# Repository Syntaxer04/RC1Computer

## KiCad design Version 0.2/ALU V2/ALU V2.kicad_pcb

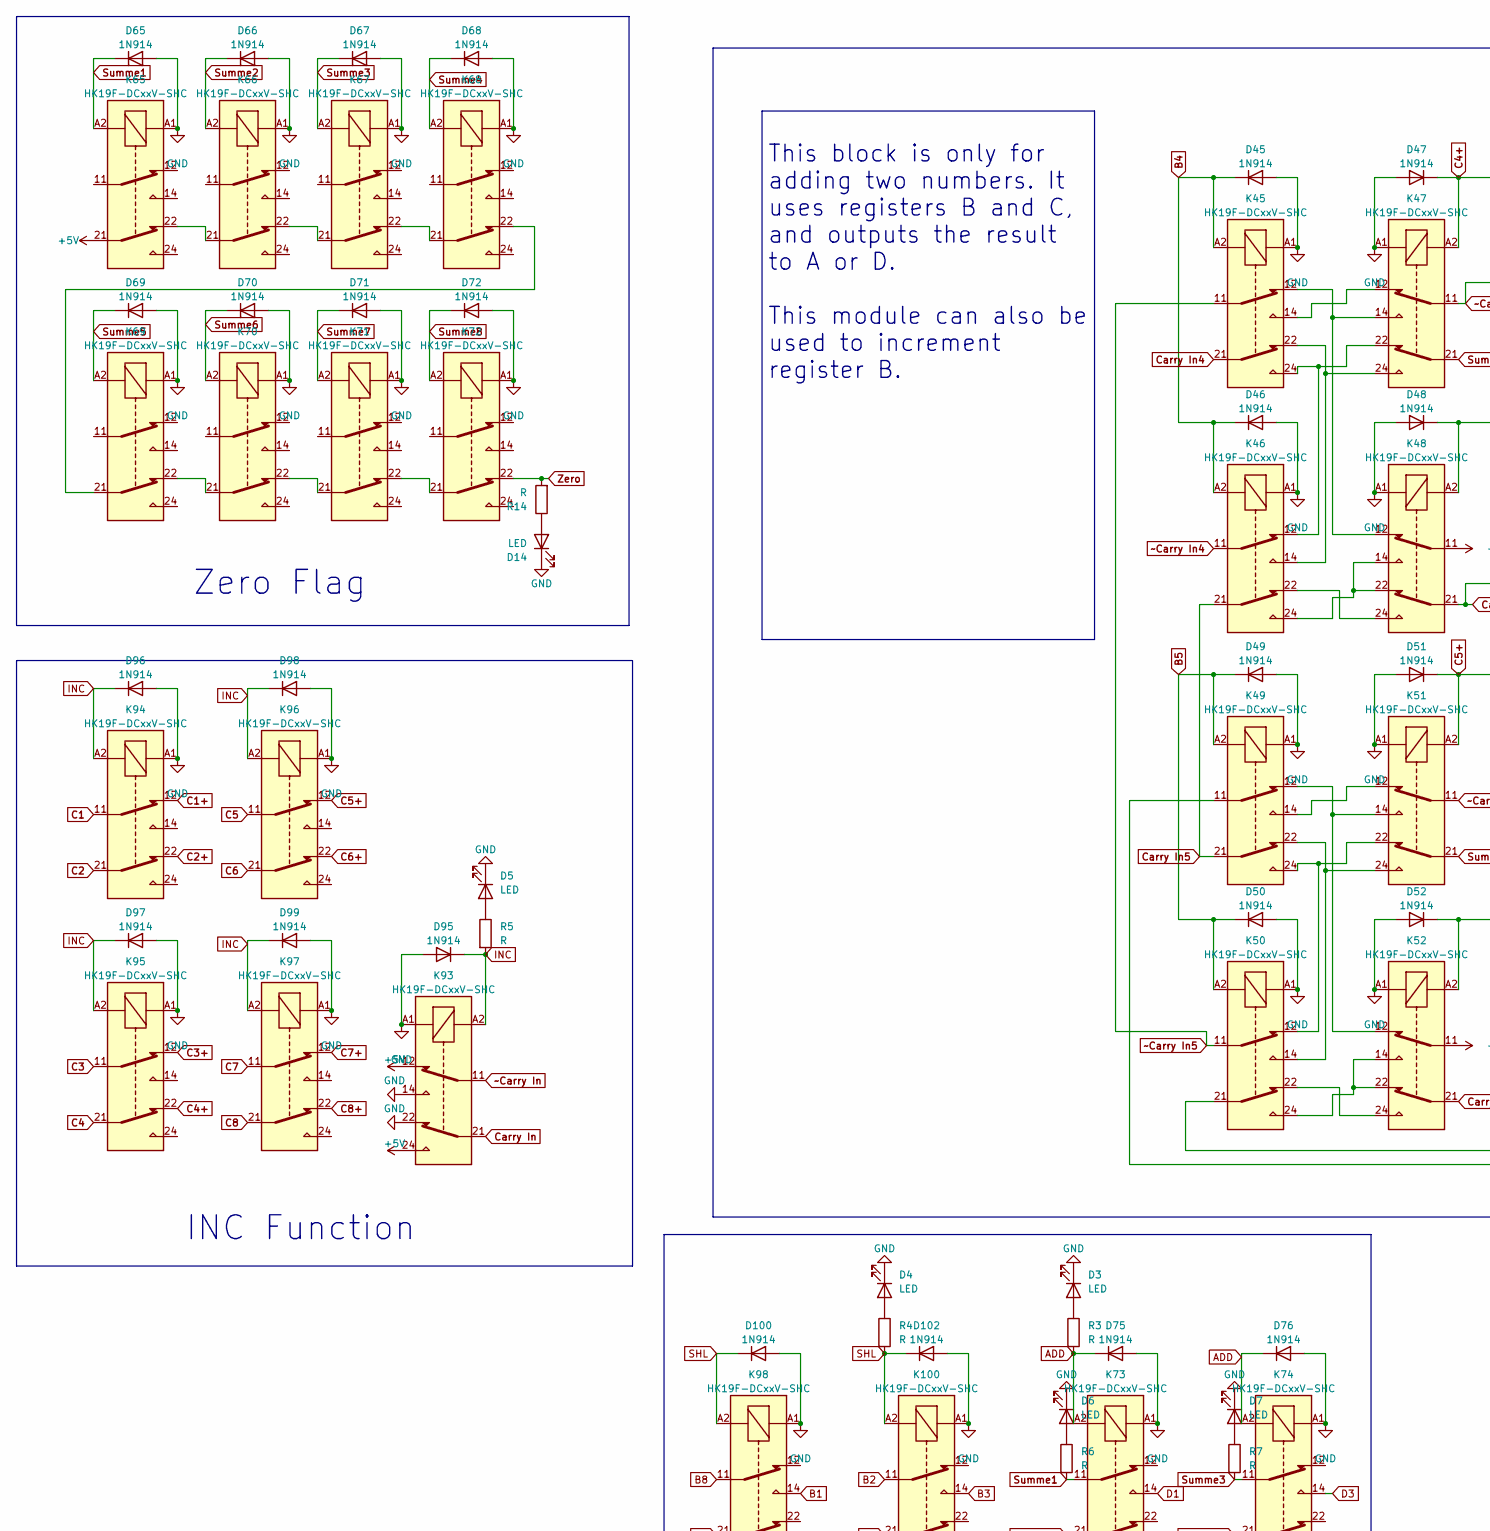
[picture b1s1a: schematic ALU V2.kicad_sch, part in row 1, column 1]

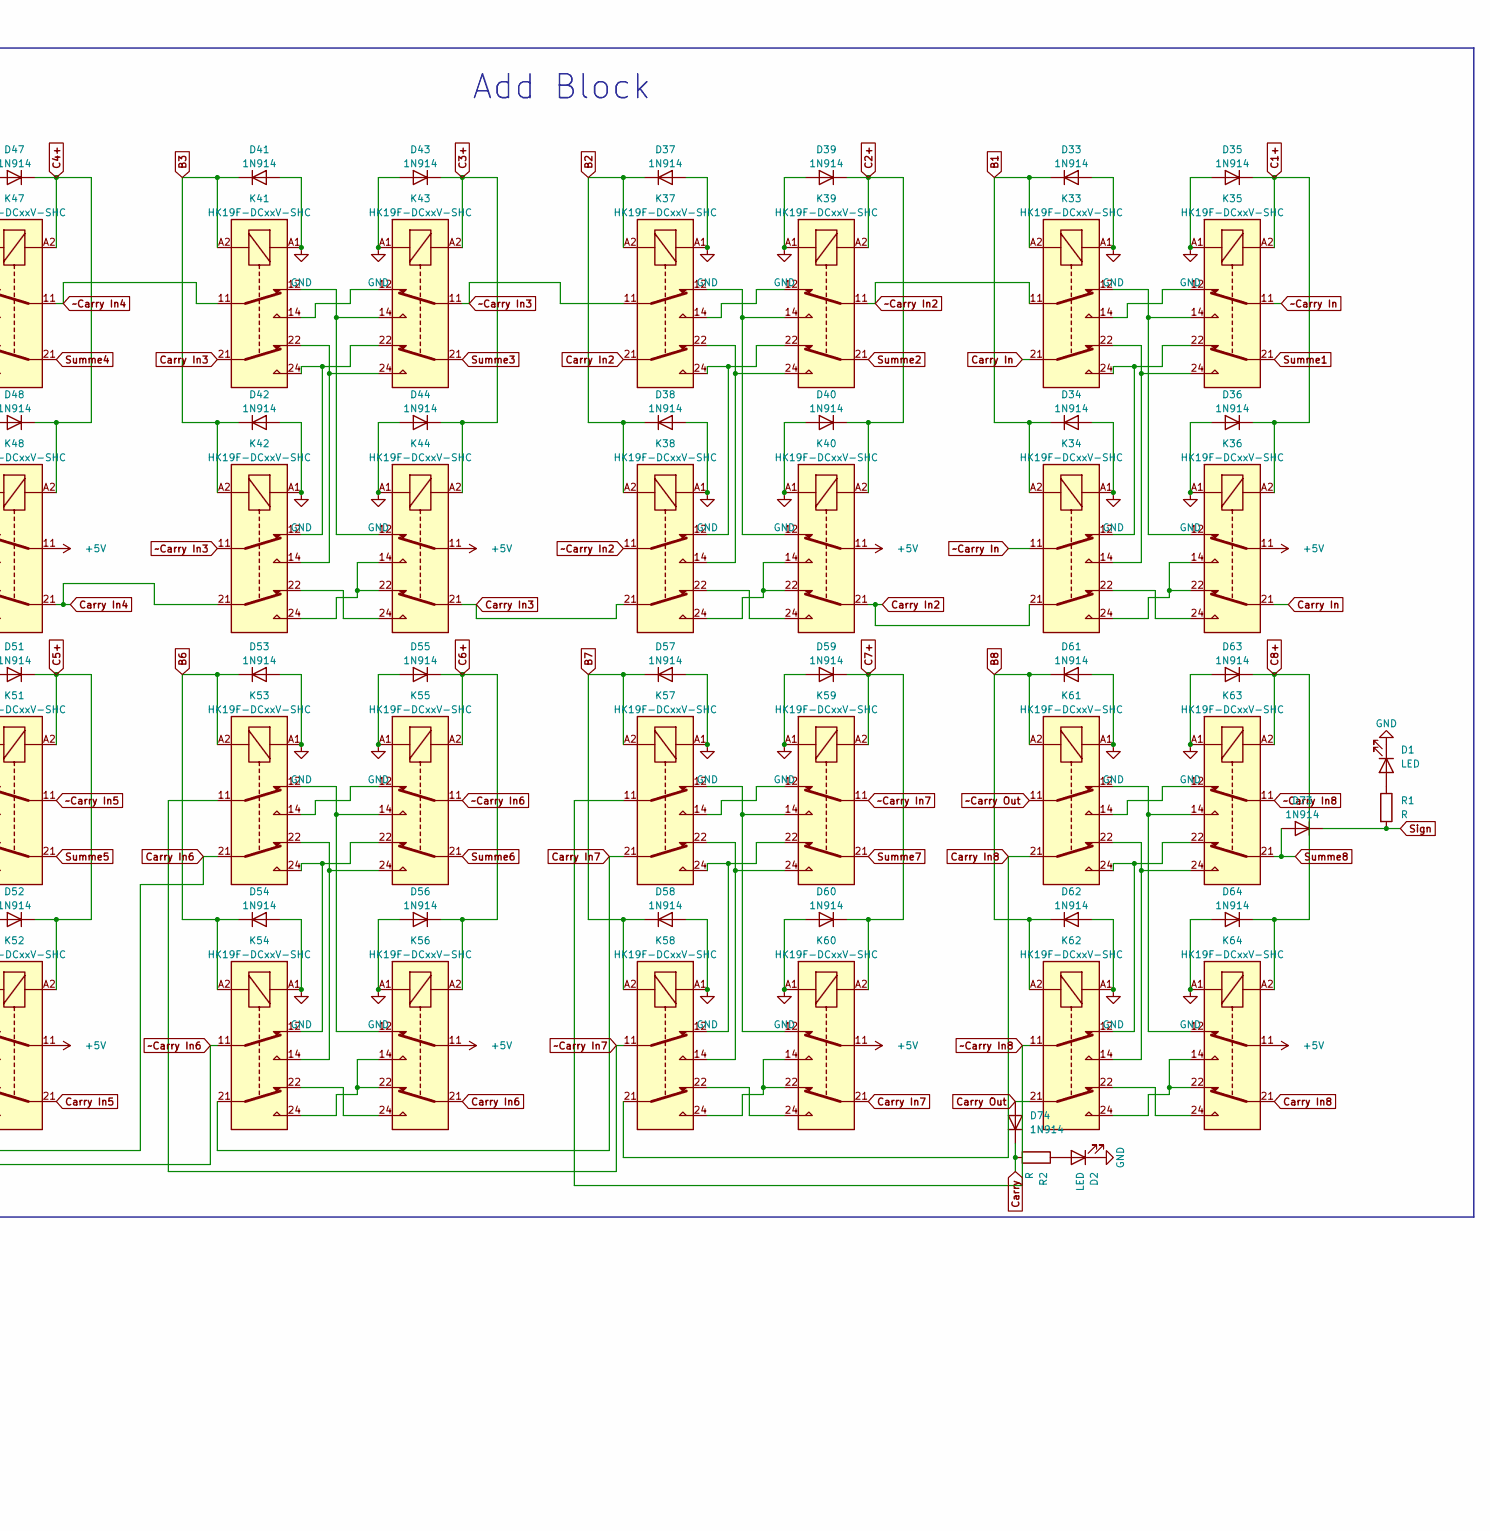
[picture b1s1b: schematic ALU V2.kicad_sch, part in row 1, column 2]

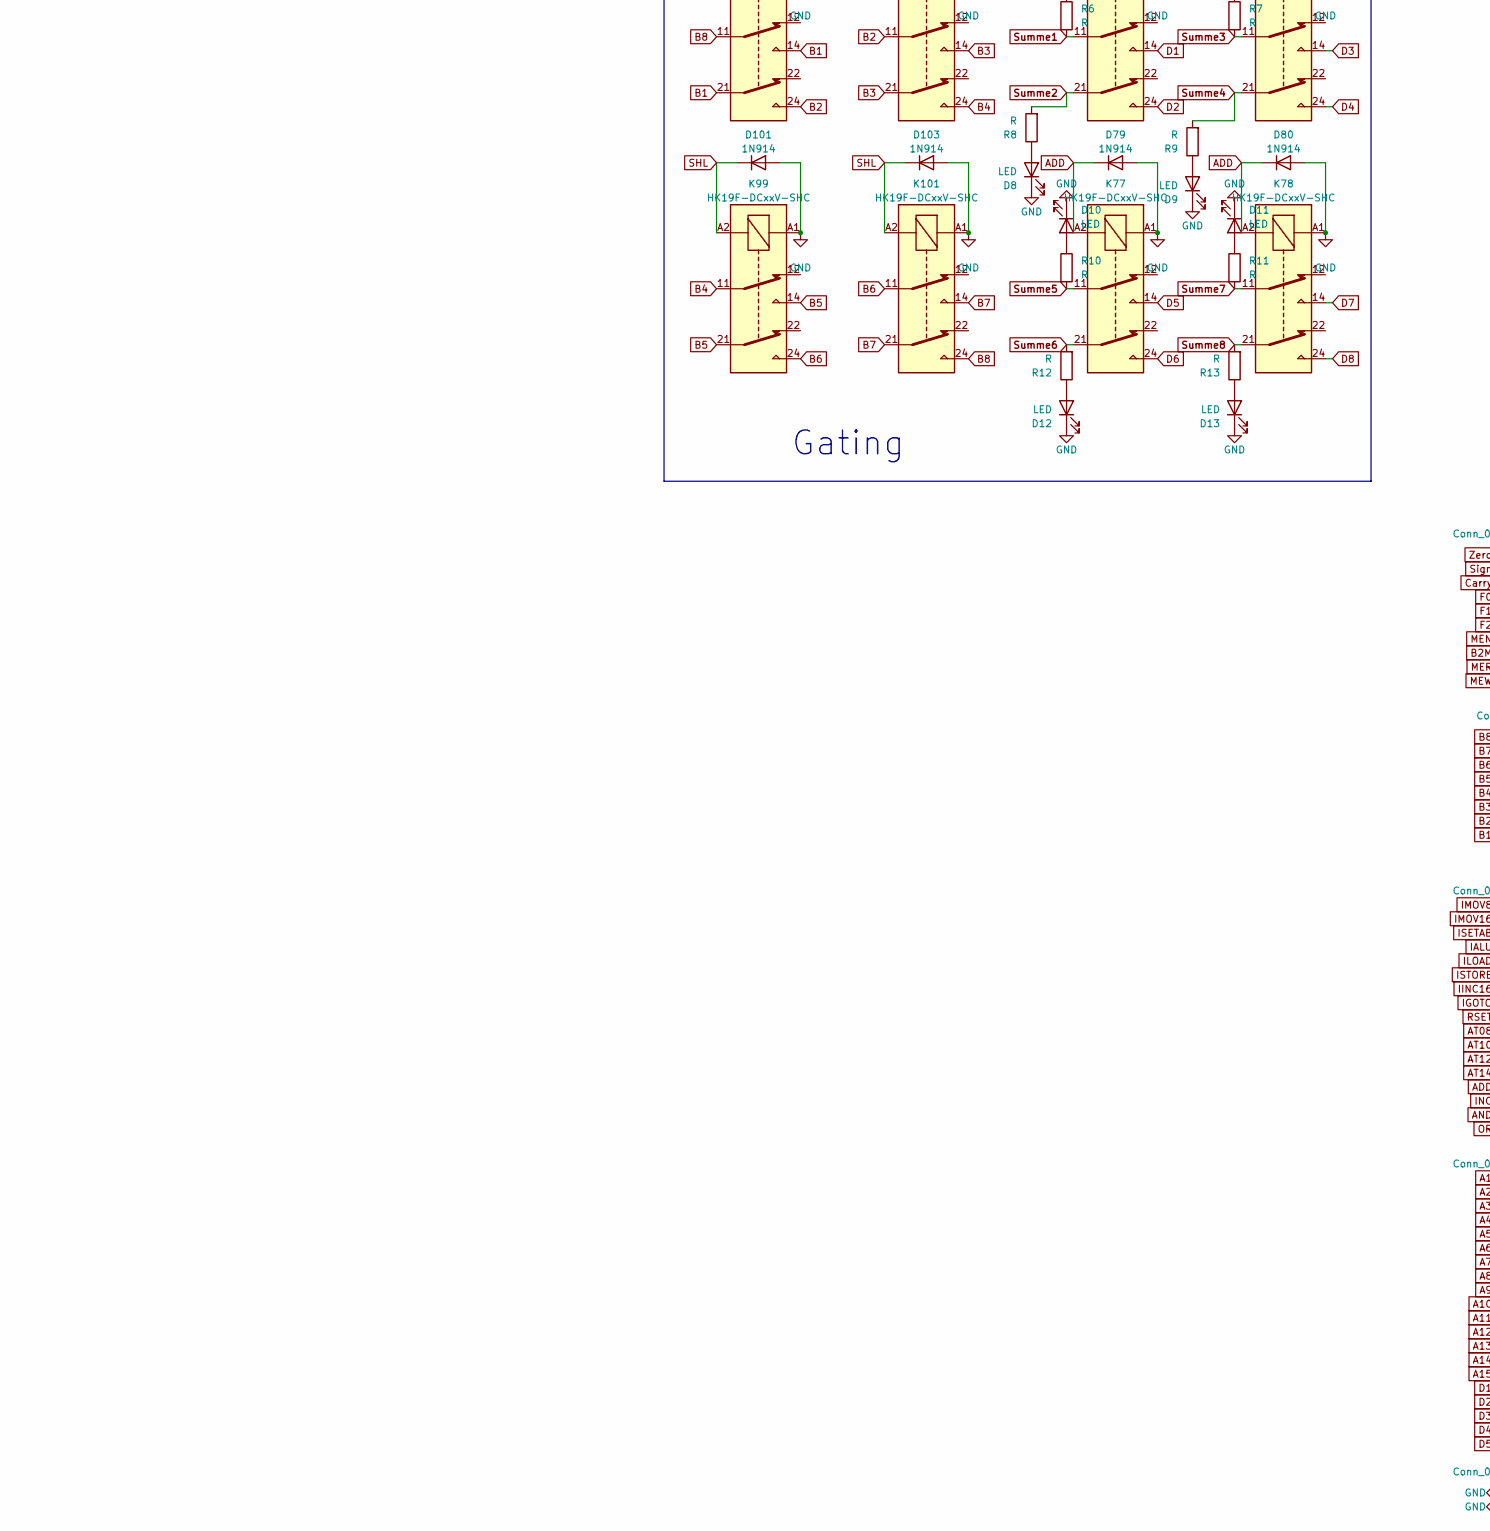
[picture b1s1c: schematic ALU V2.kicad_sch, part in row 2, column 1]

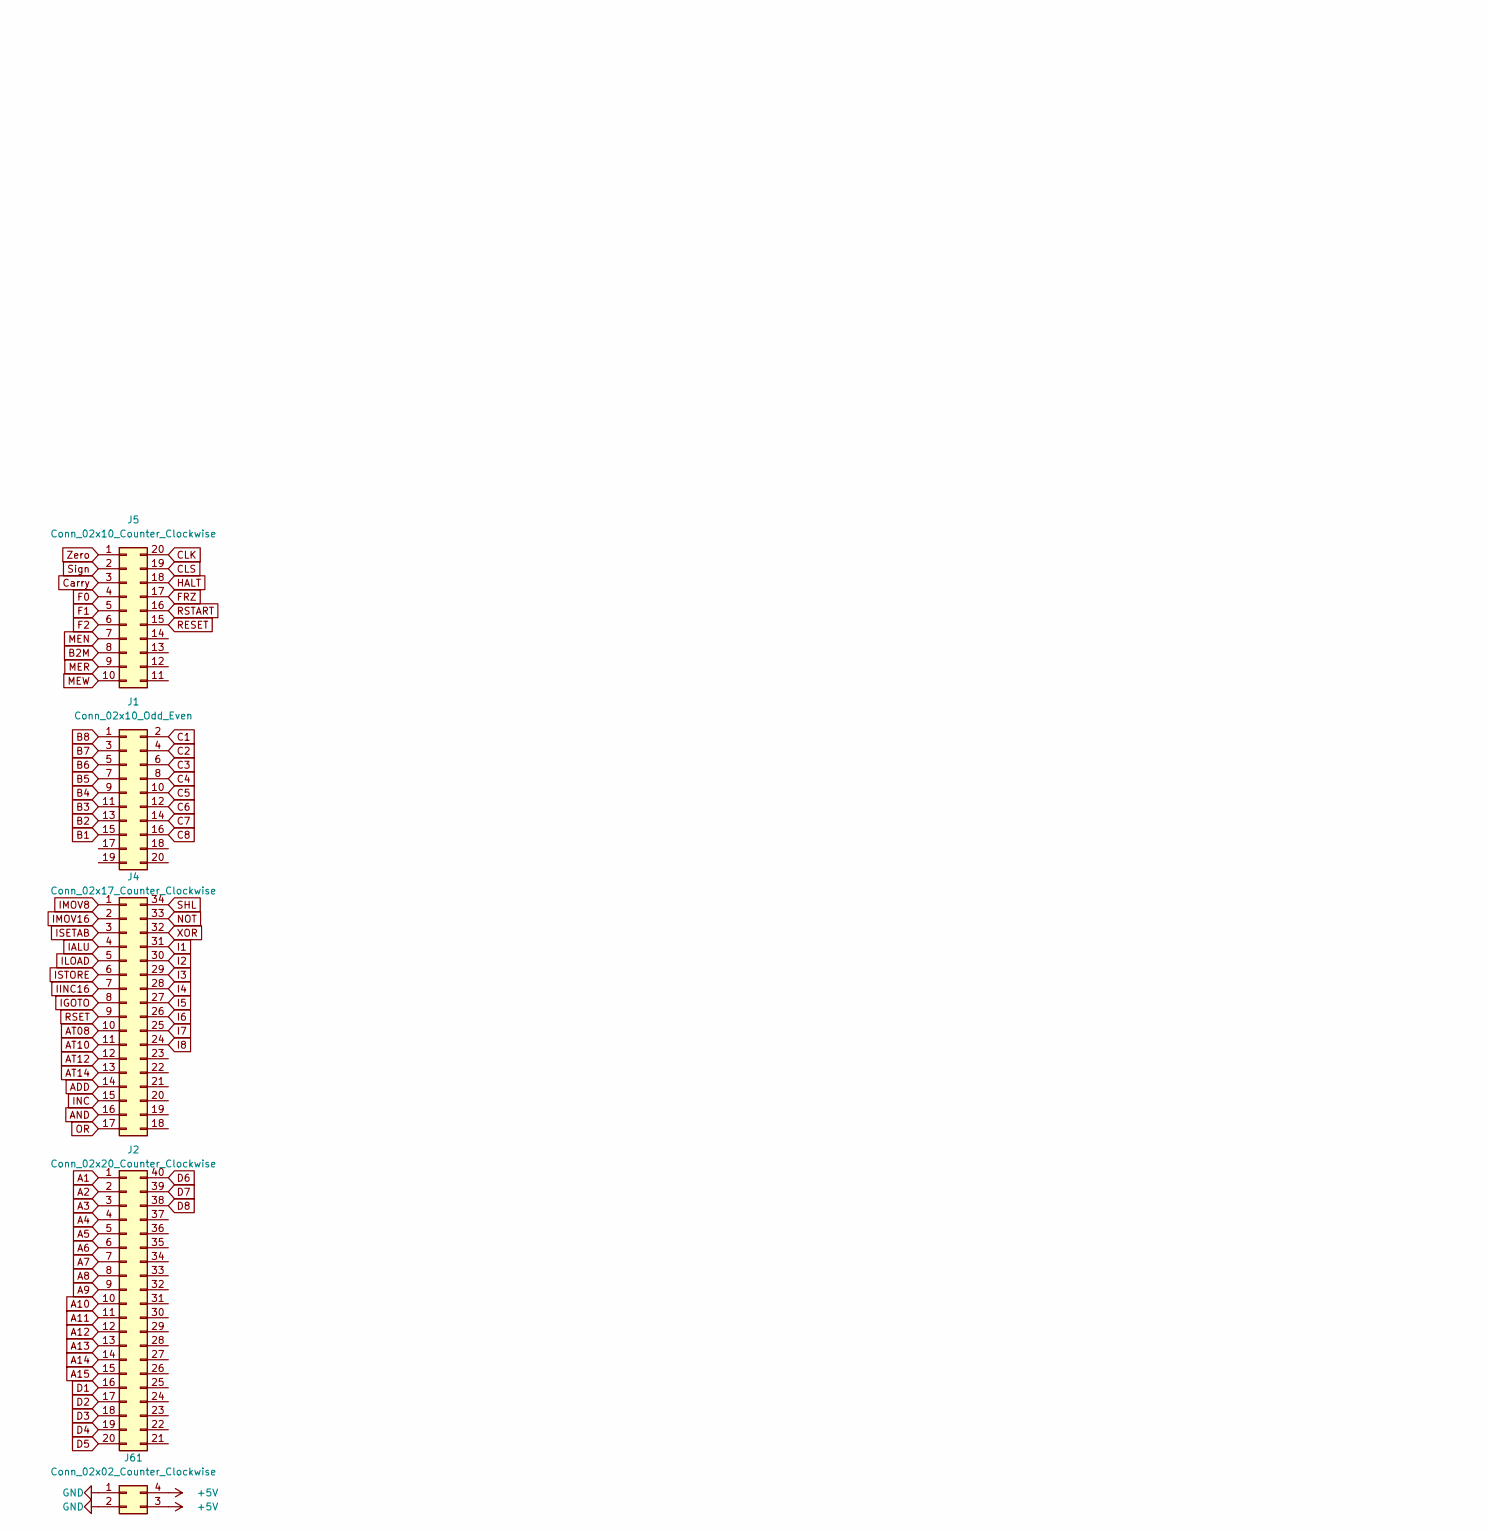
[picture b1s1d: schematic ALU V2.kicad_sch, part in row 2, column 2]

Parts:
D1, D2, D3, D4, D5, D6, D7, D8, D9, D10, D11, D12, D13, D14: LED; LED_D5.0mm
D33, D34, D35, D36, D37, D38, D39, D40, D41, D42, D43, D44, D45, D46, D47, D48, D49, D50, D51, D52, D53, D54, D55, D56, D57, D58, D59, D60, D61, D62, D63, D64, D65, D66, D67, D68, D69, D70, D71, D72, D73, D74, D75, D76, D79, D80, D95, D96, D97, D98, D99, D100, D101, D102, D103: 1N914; D_DO-35_SOD27_P7.62mm_Horizontal
J1: Conn_02x10_Odd_Even; PinHeader_2x10_P2.54mm_Horizontal
J2: Conn_02x20_Counter_Clockwise; PinSocket_2x20_P2.54mm_Horizontal
J4: Conn_02x17_Counter_Clockwise; PinSocket_2x17_P2.54mm_Horizontal
J5: Conn_02x10_Counter_Clockwise; PinSocket_2x10_P2.54mm_Horizontal
J61: Conn_02x02_Counter_Clockwise; PinSocket_2x02_P2.54mm_Horizontal
K33, K34, K35, K36, K37, K38, K39, K40, K41, K42, K43, K44, K45, K46, K47, K48, K49, K50, K51, K52, K53, K54, K55, K56, K57, K58, K59, K60, K61, K62, K63, K64, K65, K66, K67, K68, K69, K70, K71, K72, K73, K74, K77, K78, K93, K94, K95, K96, K97, K98, K99, K100, K101: HK19F-DCxxV-SHC; Relay_DPDT_Finder_30.22
R1, R2, R3, R4, R5, R6, R7, R8, R9, R10, R11, R12, R13, R14: R; R_Axial_DIN0204_L3.6mm_D1.6mm_P5.08mm_Horizontal

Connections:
+5V: J61.3, J61.4, K36.11, K40.11, K44.11, K48.11, K52.11, K56.11, K60.11, K64.11, K65.21, K93.12, K93.24
A1: J2.1
A2: J2.2
A3: J2.3
A4: J2.4
A5: J2.5
A6: J2.6
A7: J2.7
A8: J2.8
A9: J2.9
A10: J2.10
A11: J2.11
A12: J2.12
A13: J2.13
A14: J2.14
A15: J2.15
ADD: D75.1 (K), D76.1 (K), D79.1 (K), D80.1 (K), J4.14, K73.A2, K74.A2, K77.A2, K78.A2, R3.2
AND: J4.16
AT08: J4.10
AT10: J4.11
AT12: J4.12
AT14: J4.13
B1: D33.1 (K), D34.1 (K), J1.15, K33.A2, K34.A2, K98.14, K98.21
B2: D37.1 (K), D38.1 (K), J1.13, K37.A2, K38.A2, K98.24, K100.11
B2M: J5.8
B3: D41.1 (K), D42.1 (K), J1.11, K41.A2, K42.A2, K100.14, K100.21
B4: D45.1 (K), D46.1 (K), J1.9, K45.A2, K46.A2, K99.11, K100.24
B5: D49.1 (K), D50.1 (K), J1.7, K49.A2, K50.A2, K99.14, K99.21
B6: D53.1 (K), D54.1 (K), J1.5, K53.A2, K54.A2, K99.24, K101.11
B7: D57.1 (K), D58.1 (K), J1.3, K57.A2, K58.A2, K101.14, K101.21
B8: D61.1 (K), D62.1 (K), J1.1, K61.A2, K62.A2, K98.11, K101.24
C1: J1.2, K94.11
C1+: D35.1 (K), D36.1 (K), K35.A2, K36.A2, K94.12
C2: J1.4, K94.21
C2+: D39.1 (K), D40.1 (K), K39.A2, K40.A2, K94.22
C3: J1.6, K95.11
C3+: D43.1 (K), D44.1 (K), K43.A2, K44.A2, K95.12
C4: J1.8, K95.21
C4+: D47.1 (K), D48.1 (K), K47.A2, K48.A2, K95.22
C5: J1.10, K96.11
C5+: D51.1 (K), D52.1 (K), K51.A2, K52.A2, K96.12
C6: J1.12, K96.21
C6+: D55.1 (K), D56.1 (K), K55.A2, K56.A2, K96.22
C7: J1.14, K97.11
C7+: D59.1 (K), D60.1 (K), K59.A2, K60.A2, K97.12
C8: J1.16, K97.21
C8+: D63.1 (K), D64.1 (K), K63.A2, K64.A2, K97.22
CLK: J5.20
CLS: J5.19
Carry: D74.1 (K), J5.3, R2.2
Carry In: K33.21, K36.21, K93.21
Carry In2: K34.21, K37.21, K40.21
Carry In3: K38.21, K41.21, K44.21
Carry In4: K42.21, K45.21, K48.21
Carry In5: K46.21, K49.21, K52.21
Carry In6: K50.21, K53.21, K56.21
Carry In7: K54.21, K57.21, K60.21
Carry In8: K58.21, K61.21, K64.21
Carry Out: D74.2 (A), K62.21
D1: J2.16, K73.14
D2: J2.17, K73.24
D3: J2.18, K74.14
D4: J2.19, K74.24
D5: J2.20, K77.14
D6: J2.40, K77.24
D7: J2.39, K78.14
D8: J2.38, K78.24
F0: J5.4
F1: J5.5
F2: J5.6
FRZ: J5.17
GND: D1.1 (K), D2.1 (K), D3.1 (K), D4.1 (K), D5.1 (K), D6.1 (K), D7.1 (K), D8.1 (K), D9.1 (K), D10.1 (K), D11.1 (K), D12.1 (K), D13.1 (K), D14.1 (K), D33.2 (A), D34.2 (A), D35.2 (A), D36.2 (A), D37.2 (A), D38.2 (A), D39.2 (A), D40.2 (A), D41.2 (A), D42.2 (A), D43.2 (A), D44.2 (A), D45.2 (A), D46.2 (A), D47.2 (A), D48.2 (A), D49.2 (A), D50.2 (A), D51.2 (A), D52.2 (A), D53.2 (A), D54.2 (A), D55.2 (A), D56.2 (A), D57.2 (A), D58.2 (A), D59.2 (A), D60.2 (A), D61.2 (A), D62.2 (A), D63.2 (A), D64.2 (A), D65.2 (A), D66.2 (A), D67.2 (A), D68.2 (A), D69.2 (A), D70.2 (A), D71.2 (A), D72.2 (A), D75.2 (A), D76.2 (A), D79.2 (A), D80.2 (A), D95.2 (A), D96.2 (A), D97.2 (A), D98.2 (A), D99.2 (A), D100.2 (A), D101.2 (A), D102.2 (A), D103.2 (A), J61.1, J61.2, K33.A1, K34.A1, K35.A1, K36.A1, K37.A1, K38.A1, K39.A1, K40.A1, K41.A1, K42.A1, K43.A1, K44.A1, K45.A1, K46.A1, K47.A1, K48.A1, K49.A1, K50.A1, K51.A1, K52.A1, K53.A1, K54.A1, K55.A1, K56.A1, K57.A1, K58.A1, K59.A1, K60.A1, K61.A1, K62.A1, K63.A1, K64.A1, K65.A1, K66.A1, K67.A1, K68.A1, K69.A1, K70.A1, K71.A1, K72.A1, K73.A1, K74.A1, K77.A1, K78.A1, K93.14, K93.22, K93.A1, K94.A1, K95.A1, K96.A1, K97.A1, K98.A1, K99.A1, K100.A1, K101.A1
HALT: J5.18
I1: J4.31
I2: J4.30
I3: J4.29
I4: J4.28
I5: J4.27
I6: J4.26
I7: J4.25
I8: J4.24
IALU: J4.4
IGOTO: J4.8
IINC16: J4.7
ILOAD: J4.5
IMOV8: J4.1
IMOV16: J4.2
INC: D95.1 (K), D96.1 (K), D97.1 (K), D98.1 (K), D99.1 (K), J4.15, K93.A2, K94.A2, K95.A2, K96.A2, K97.A2, R5.2
ISETAB: J4.3
ISTORE: J4.6
MEN: J5.7
MER: J5.9
MEW: J5.10
NOT: J4.33
unnamed: D1.2 (A), R1.1
unnamed: D2.2 (A), R2.1
unnamed: D3.2 (A), R3.1
unnamed: D4.2 (A), R4.1
unnamed: D5.2 (A), R5.1
unnamed: D6.2 (A), R6.1
unnamed: D7.2 (A), R7.1
unnamed: D8.2 (A), R8.1
unnamed: D9.2 (A), R9.1
unnamed: D10.2 (A), R10.1
unnamed: D11.2 (A), R11.1
unnamed: D12.2 (A), R12.1
unnamed: D13.2 (A), R13.1
unnamed: D14.2 (A), R14.1
unnamed: K33.12, K35.14, K36.12
unnamed: K33.14, K35.12
unnamed: K33.22, K34.14, K35.24
unnamed: K33.24, K34.12, K35.22
unnamed: K34.22, K36.24
unnamed: K34.24, K36.14, K36.22
unnamed: K37.12, K39.14, K40.12
unnamed: K37.14, K39.12
unnamed: K37.22, K38.14, K39.24
unnamed: K37.24, K38.12, K39.22
unnamed: K38.22, K40.24
unnamed: K38.24, K40.14, K40.22
unnamed: K41.12, K43.14, K44.12
unnamed: K41.14, K43.12
unnamed: K41.22, K42.14, K43.24
unnamed: K41.24, K42.12, K43.22
unnamed: K42.22, K44.24
unnamed: K42.24, K44.14, K44.22
unnamed: K45.12, K47.14, K48.12
unnamed: K45.14, K47.12
unnamed: K45.22, K46.14, K47.24
unnamed: K45.24, K46.12, K47.22
unnamed: K46.22, K48.24
unnamed: K46.24, K48.14, K48.22
unnamed: K49.12, K51.14, K52.12
unnamed: K49.14, K51.12
unnamed: K49.22, K50.14, K51.24
unnamed: K49.24, K50.12, K51.22
unnamed: K50.22, K52.24
unnamed: K50.24, K52.14, K52.22
unnamed: K53.12, K55.14, K56.12
unnamed: K53.14, K55.12
unnamed: K53.22, K54.14, K55.24
unnamed: K53.24, K54.12, K55.22
unnamed: K54.22, K56.24
unnamed: K54.24, K56.14, K56.22
unnamed: K57.12, K59.14, K60.12
unnamed: K57.14, K59.12
unnamed: K57.22, K58.14, K59.24
unnamed: K57.24, K58.12, K59.22
unnamed: K58.22, K60.24
unnamed: K58.24, K60.14, K60.22
unnamed: K61.12, K63.14, K64.12
unnamed: K61.14, K63.12
unnamed: K61.22, K62.14, K63.24
unnamed: K61.24, K62.12, K63.22
unnamed: K62.22, K64.24
unnamed: K62.24, K64.14, K64.22
unnamed: K65.22, K66.21
unnamed: K66.22, K67.21
unnamed: K67.22, K68.21
unnamed: K68.22, K69.21
unnamed: K69.22, K70.21
unnamed: K70.22, K71.21
unnamed: K71.22, K72.21
OR: J4.17
RESET: J5.15
RSET: J4.9
RSTART: J5.16
SHL: D100.1 (K), D101.1 (K), D102.1 (K), D103.1 (K), J4.34, K98.A2, K99.A2, K100.A2, K101.A2, R4.2
Sign: D73.1 (K), J5.2, R1.2
Summe1: D65.1 (K), K35.21, K65.A2, K73.11, R6.2
Summe2: D66.1 (K), K39.21, K66.A2, K73.21, R8.2
Summe3: D67.1 (K), K43.21, K67.A2, K74.11, R7.2
Summe4: D68.1 (K), K47.21, K68.A2, K74.21, R9.2
Summe5: D69.1 (K), K51.21, K69.A2, K77.11, R10.2
Summe6: D70.1 (K), K55.21, K70.A2, K77.21, R12.2
Summe7: D71.1 (K), K59.21, K71.A2, K78.11, R11.2
Summe8: D72.1 (K), D73.2 (A), K63.21, K72.A2, K78.21, R13.2
XOR: J4.32
Zero: J5.1, K72.22, R14.2
~Carry In: K34.11, K35.11, K93.11
~Carry In2: K33.11, K38.11, K39.11
~Carry In3: K37.11, K42.11, K43.11
~Carry In4: K41.11, K46.11, K47.11
~Carry In5: K45.11, K50.11, K51.11
~Carry In6: K49.11, K54.11, K55.11
~Carry In7: K53.11, K58.11, K59.11
~Carry In8: K57.11, K62.11, K63.11
~Carry Out: K61.11

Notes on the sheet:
Add Block
INC Function
Gating
Zero Flag
This block is only for adding two numbers. It uses registers B and C, and outputs the result to A or D. This module can also be used to increment register B.

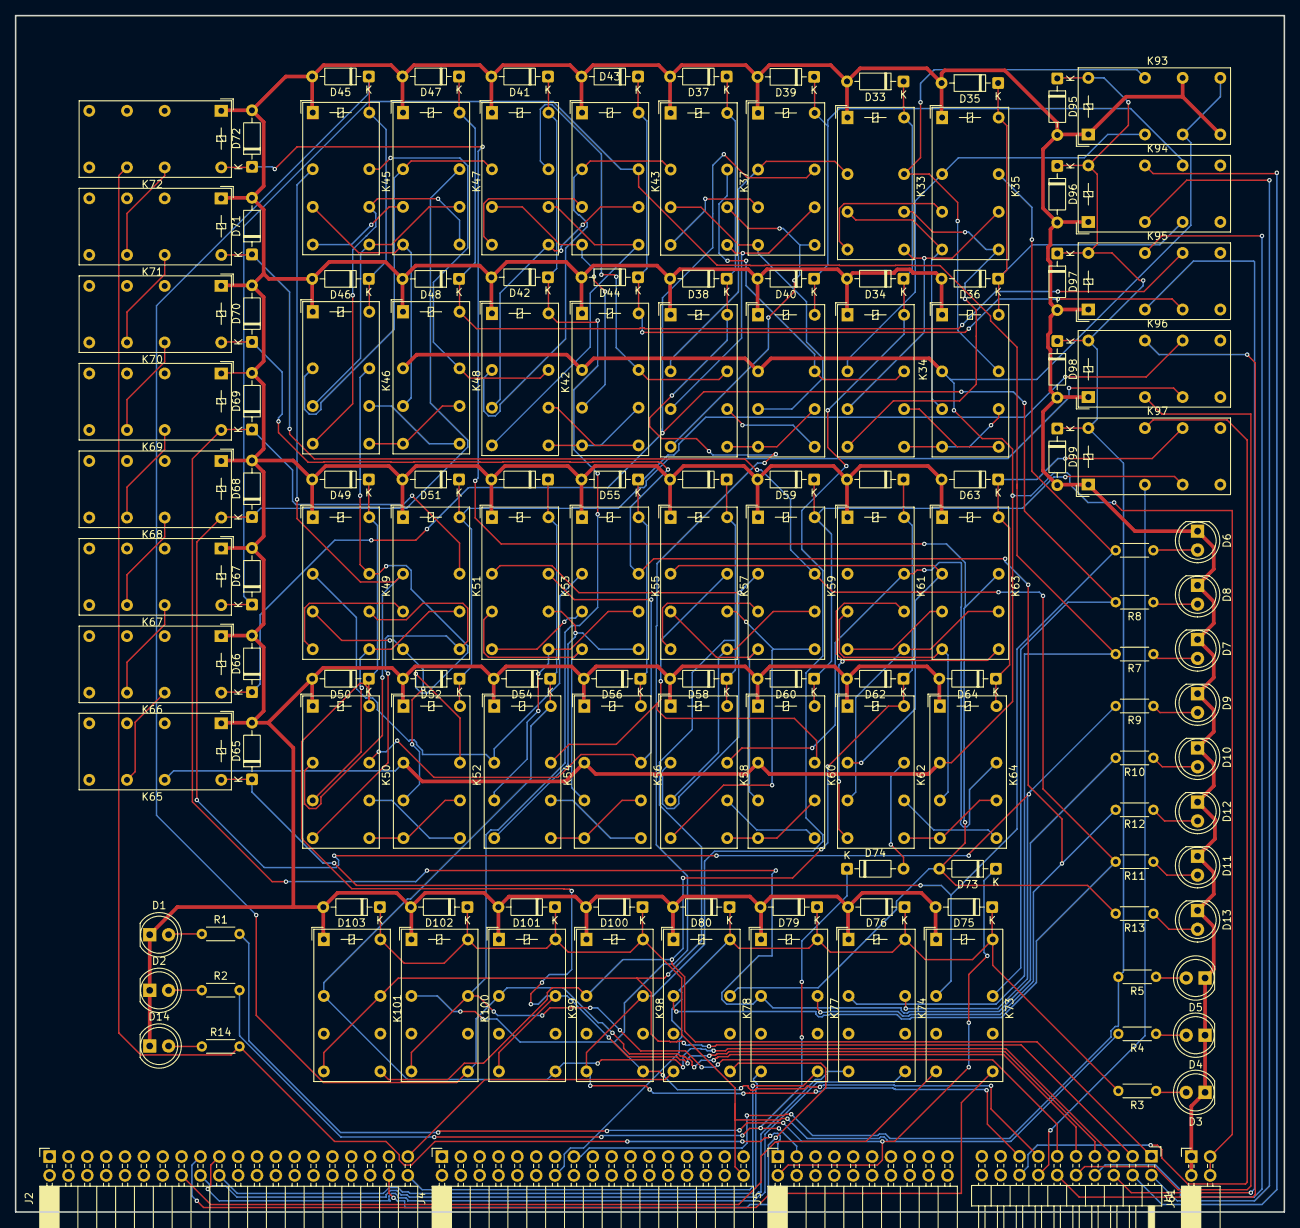
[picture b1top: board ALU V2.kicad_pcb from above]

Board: 2 copper layers, 170.9 x 161.2 mm, 141 parts (0 on the bottom side), 134 nets.
